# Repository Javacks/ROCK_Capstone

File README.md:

# ROCK_Capstone_Project
 This repository contains the electrical (only) designs made by me. 

 # The Objective
 The purpose of the project is to create an cave ROV (Remote Operated Vehicle) explorer capable of handling temperatures up to 50°C. This with the intent to avoid miners to traverse dangerous zones where heat or dangerous gases are present. The ROV is able to traverse up to 50m in distance, by controlling it safely at a central computer. The computer and the ROV are communicating through a CAT6 (Ethernet) cable.

 # Some Technical Details
The ROV is able to measure 4 different gases known to damage the human body: $CH_4, $CO_2, CO, H_2S$.
- All gases are measured in ppm (parts per million)
- All gases readings are in real time

Due to different power rails, and different demands, this project contains a custom __daughter board for the STM32: NUCLEO-64 STM32F446RE__. The document refers this custom PCB as the "STM32_Shield".

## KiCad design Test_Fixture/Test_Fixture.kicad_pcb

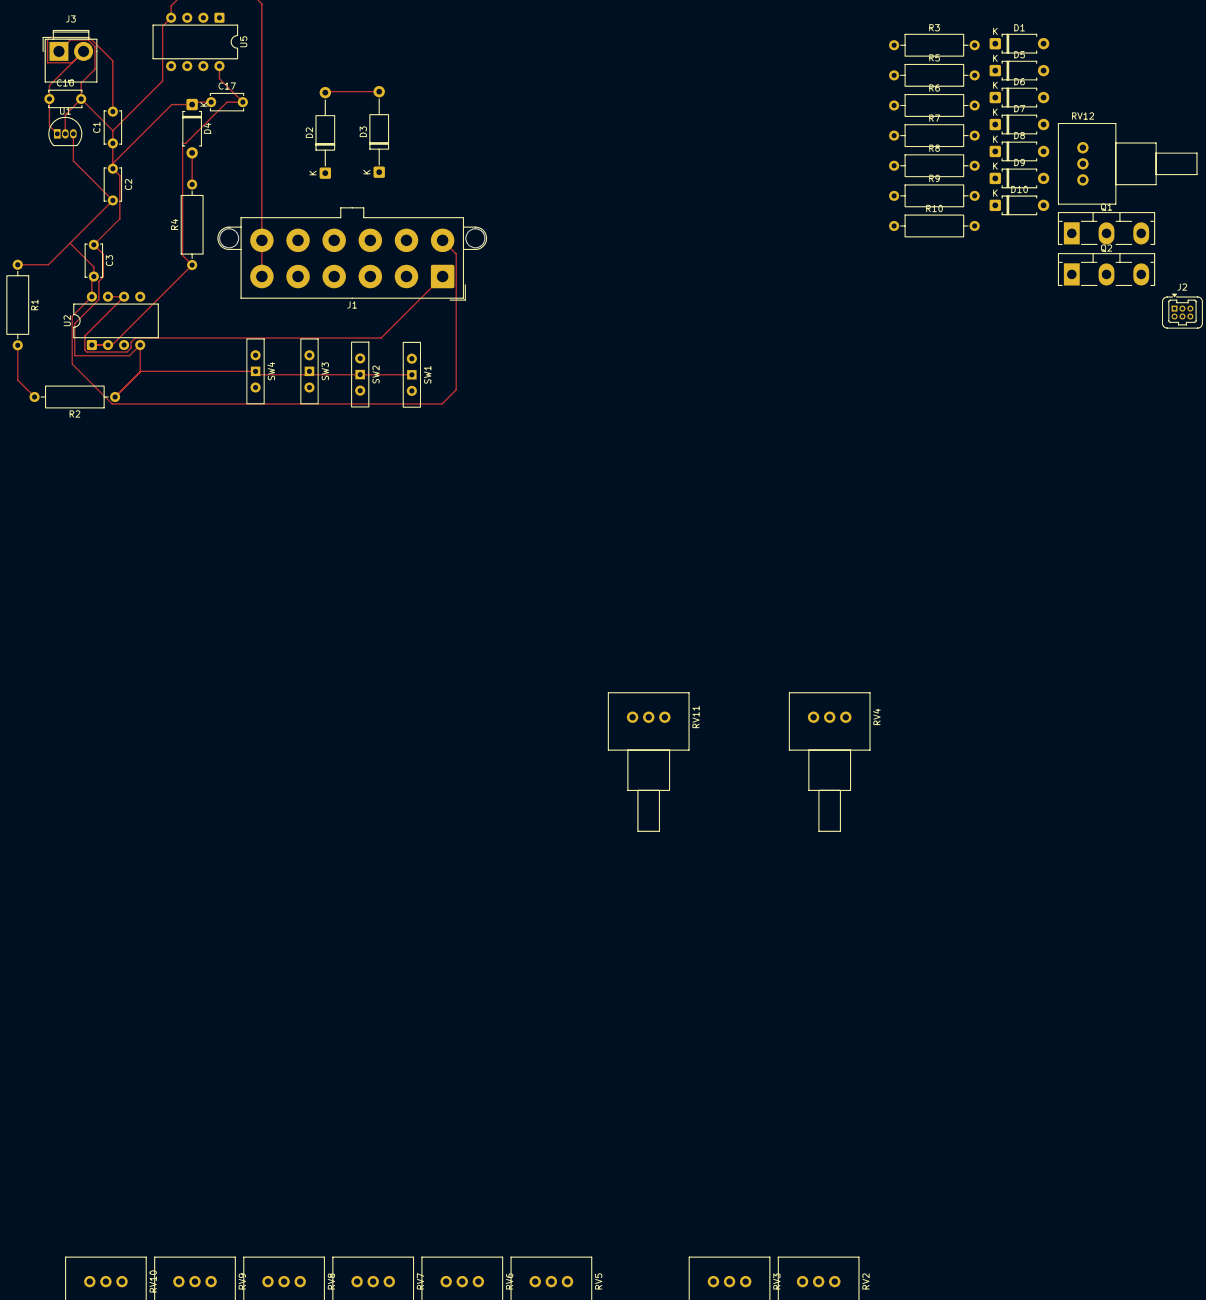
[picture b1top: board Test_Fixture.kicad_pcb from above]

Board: 2 copper layers, 48 parts (0 on the bottom side), 36 nets.

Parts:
C1, C2: 0.2; C_Disc_D5.0mm_W2.5mm_P5.00mm
C3, C17: 0.1; C_Disc_D5.0mm_W2.5mm_P5.00mm
C16: 100; C_Disc_D5.0mm_W2.5mm_P5.00mm
D1, D4, D5, D6, D7, D8, D9, D10: LED; D_A-405_P7.62mm_Horizontal
D2, D3: D; D_A-405_P12.70mm_Horizontal
J1: Analog Signals; Molex_Mega-Fit_76829-0012_2x06_P5.70mm_Vertical
J2: Digital Signals; Harwin_Gecko-G125-FVX0605L0X_2x03_P1.25mm_Vertical
J3: Power Supply; JWT_A3963_1x02_P3.96mm_Vertical
Q1, Q2: 2N222; TO-218-3_Vertical
R1: 2.2k; R_Axial_DIN0309_L9.0mm_D3.2mm_P12.70mm_Horizontal
R2: 4.7k; R_Axial_DIN0309_L9.0mm_D3.2mm_P12.70mm_Horizontal
R3, R4, R5, R6, R7, R8, R9, R10: 220; R_Axial_DIN0309_L9.0mm_D3.2mm_P12.70mm_Horizontal
RV2, RV3, RV4, RV5, RV6, RV7, RV8, RV9, RV10: 10k; Potentiometer_Vishay_148-149_Single_Horizontal
RV11, RV12: 5k; Potentiometer_Vishay_148-149_Single_Horizontal
SW1, SW2, SW3, SW4: SW_SPST; SW_Slide-03_Wuerth-WS-SLTV_10x2.5x6.4_P2.54mm
U1: LM78L05_SO8; TO-92_Inline
U2, U5: LM358; CERDIP-8_W7.62mm_SideBrazed

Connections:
+3.3V: C17.2, D1.2 (A), D5.2 (A), D6.2 (A), D7.2 (A), D8.2 (A), R4.1, R9.1, R10.1, RV4.1, U2.1, U2.2 (-), U5.8 (V+)
+5V: C2.2, C3.2, J1.2, R1.1, U1.3 (VO), U2.8 (V+)
+24V: C1.2, C16.1, J3.2, U1.1 (VI)
/3.3_Adjust: J1.1, U2.6 (-), U2.7
/Digital & LED signals/3.3_Adjust: RV11.1, RV12.1
/Digital & LED signals/Baro_Fault: J2.6, Q2.2 (B)
/Digital & LED signals/Hum_Fault: J2.1, Q1.2 (B)
/Digital & LED signals/MotorOk: J2.4, R7.2, SW3.2 (B)
/Digital & LED signals/PowerOK: J2.5, R8.2, SW4.2 (B)
/Digital & LED signals/~Temp_Fault1: D2.1 (K), J2.2, R5.2, SW1.2 (B), U5.7
/Digital & LED signals/~Temp_Fault2: D3.1 (K), J2.3, R6.2, SW2.2 (B), U5.1
/Volt_Loss_Distance: RV2.1, RV3.1, RV5.1, RV6.1, RV7.1, RV8.1, RV9.1, RV10.1
GND: C1.1, C2.1, C3.1, C16.2, C17.1, D4.1 (K), J1.11, J1.12, J3.1, Q1.3 (E), Q2.3 (E), R2.1, RV2.3, RV3.3, RV4.3, RV5.3, RV6.3, RV7.3, RV8.3, RV9.3, RV10.3, RV11.3, RV12.3, SW1.1 (A), SW2.1 (A), SW3.1 (A), SW4.1 (A), U1.2 (GND), U2.4 (V-), U5.4 (V-)
unnamed: D1.1 (K), R3.1
unnamed: D2.2 (A), D3.2 (A), R3.2
unnamed: D4.2 (A), R4.2
unnamed: D5.1 (K), R5.1
unnamed: D6.1 (K), R6.1
unnamed: D7.1 (K), R7.1
unnamed: D8.1 (K), R8.1
unnamed: D9.2 (A), R10.2
unnamed: D9.1 (K), Q1.1 (C)
unnamed: D10.2 (A), R9.2
unnamed: D10.1 (K), Q2.1 (C)
unnamed: J1.5, RV5.2
unnamed: J1.6, RV2.2
unnamed: J1.7, RV3.2
unnamed: J1.8, RV6.2
unnamed: J1.9, RV7.2
unnamed: J1.10, RV8.2
unnamed: R1.2, R2.2, U2.3 (+)
unnamed: RV4.2, U2.5 (+)
unnamed: RV12.2, U5.2 (-)
unnamed: RV11.2, U5.6 (-)
Temp1: J1.3, RV10.2, U5.3 (+), U5.5 (+)
Temp2: J1.4, RV9.2

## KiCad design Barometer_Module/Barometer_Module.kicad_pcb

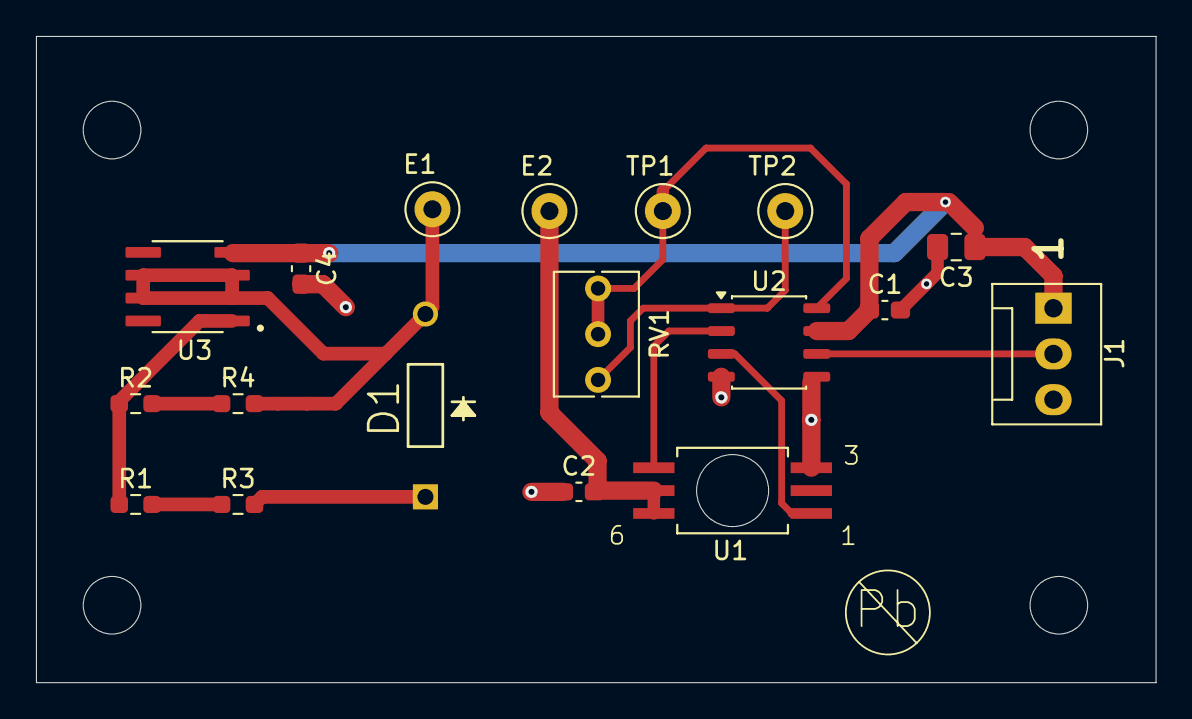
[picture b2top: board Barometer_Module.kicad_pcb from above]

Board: 2 copper layers, 62.2 x 35.9 mm, 22 parts (0 on the bottom side), 13 nets.

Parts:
C1, C2, C4: 0.1u; C_0603_1608Metric_Pad1.08x0.95mm_HandSolder
C3: 6.8u; C_0805_2012Metric_Pad1.18x1.45mm_HandSolder
D1: 1N457; DIO_1N457
E1, E2: TestPoint; TestPoint_Loop_D2.50mm_Drill1.0mm
H1, H2, H3, H4: MountingHole_Pad; MountingHole_3.2mm_M3_ISO7380
J1: 0022112032; FanPinHeader_1x03_P2.54mm_Vertical
R1: 1k; R_0603_1608Metric_Pad0.98x0.95mm_HandSolder
R2: 10k; R_0603_1608Metric_Pad0.98x0.95mm_HandSolder
R3: 330; R_0603_1608Metric_Pad0.98x0.95mm_HandSolder
R4: 3.3k; R_0603_1608Metric_Pad0.98x0.95mm_HandSolder
RV1: 10k; Potentiometer_Bourns_3266Y_Vertical
TP1, TP2: RV1; TestPoint_Loop_D2.50mm_Drill1.0mm
U1: 2SMPP-03; XDCR_2SMPP-03
U2: INA126UA; JEITA_SOIC-8_3.9x4.9mm_P1.27mm
U3: LM334MX_NOPB; SOIC127P599X175-8N

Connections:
+3.3V: C1.1, C3.1, C4.1, J1.1, U2.7 (V+), U3.4 (V+)
Earth: C1.2, C2.1, C3.2, C4.2, J1.3, U1.3 (GND), U2.4 (V-), U2.5 (Ref)
unnamed: D1.2 (A), R3.2
unnamed: D1.1 (K), E1.1, R4.2, U3.2 (V-_2), U3.3 (V-_3), U3.6 (V-_6), U3.7 (V-_7)
unnamed: J1.2, U2.6
unnamed: R1.2, R3.1
unnamed: R2.2, R4.1
unnamed: RV1.1, TP2.1, U2.1 (Rg)
unnamed: RV1.2, RV1.3, TP1.1, U2.8 (Rg)
unnamed: C2.2, E2.1, U1.5 (N-SUB), U1.6 (ICC)
unnamed: U1.1 (VOUT+), U2.3 (+)
unnamed: U1.4 (VOUT-), U2.2 (-)
unnamed: R1.1, R2.1, U3.1 (R)

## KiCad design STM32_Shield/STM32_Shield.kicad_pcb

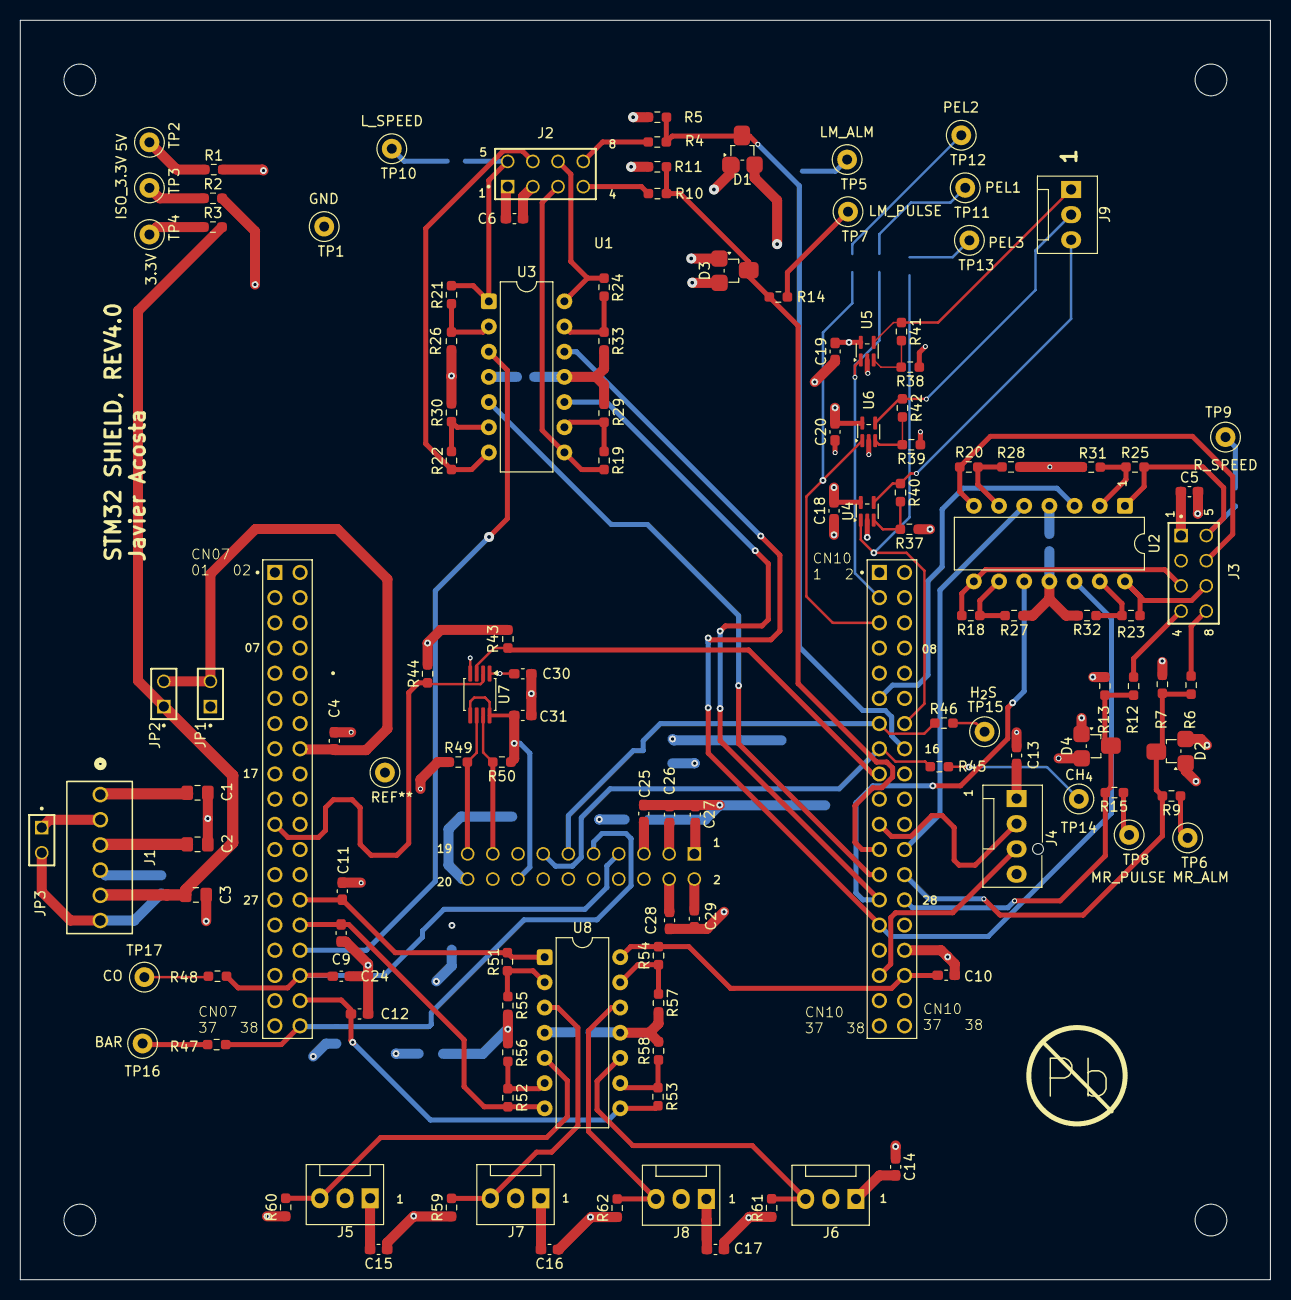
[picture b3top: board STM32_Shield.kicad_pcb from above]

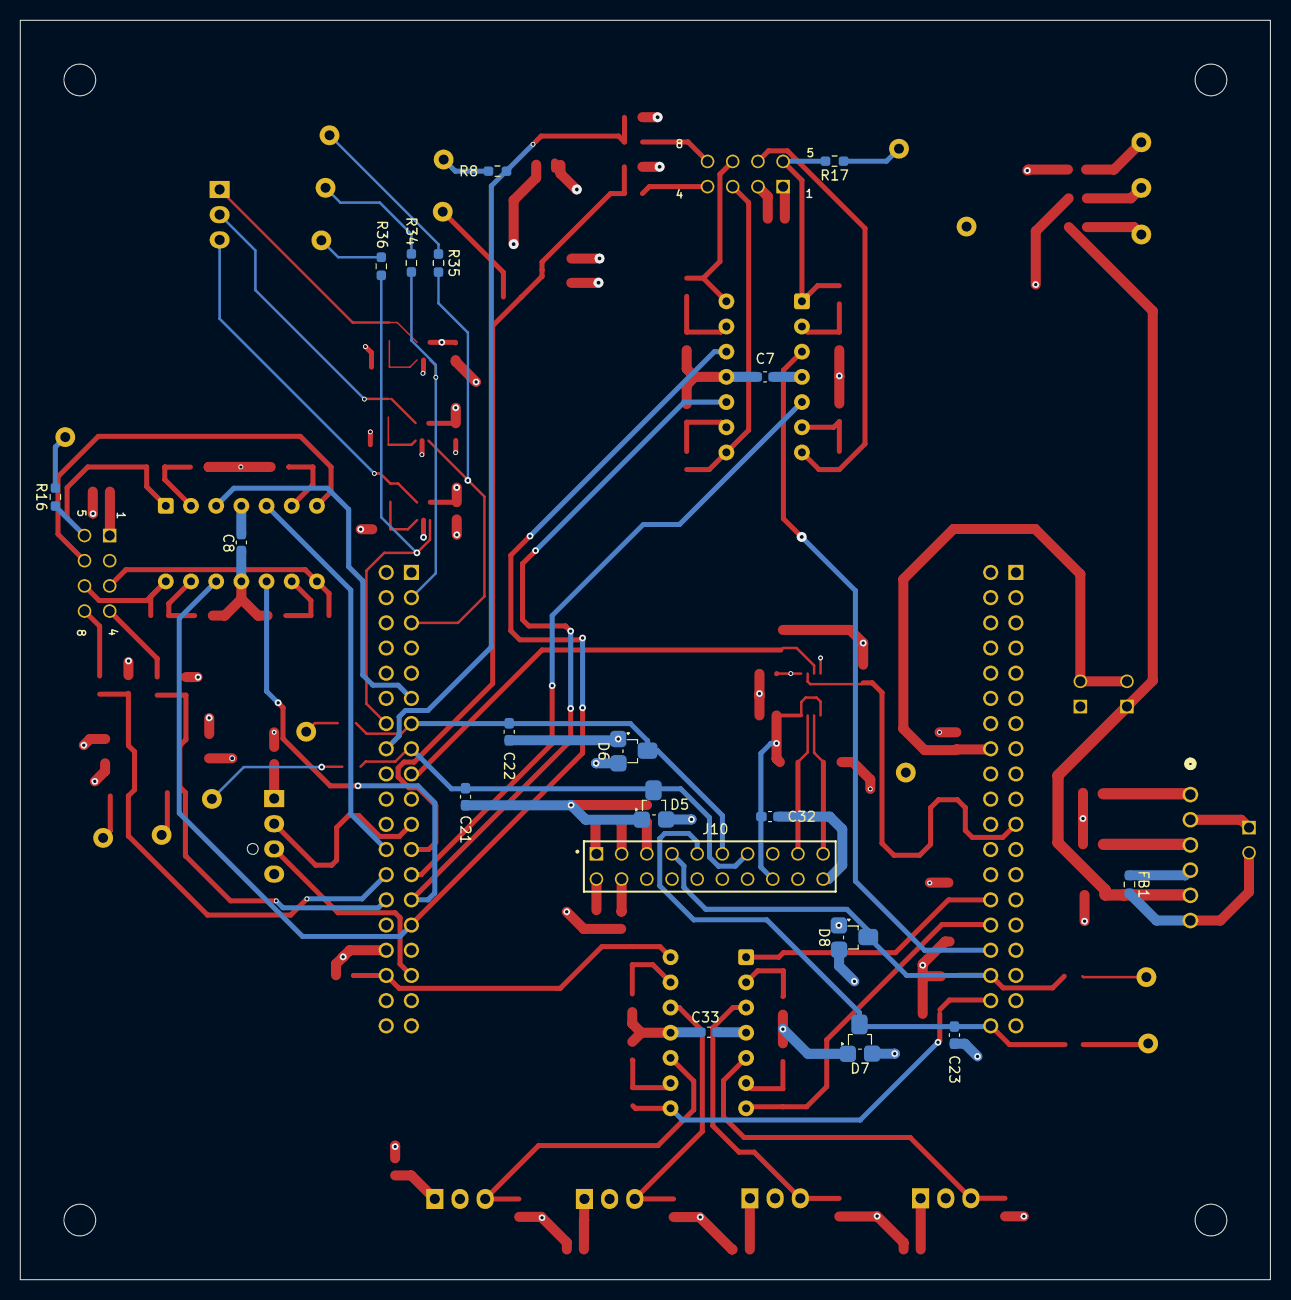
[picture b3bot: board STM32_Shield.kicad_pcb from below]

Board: 4 copper layers, 126.1 x 127.0 mm, 146 parts (19 on the bottom side), 83 nets.

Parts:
C1, C2, C3: 6.8u; C_0805_2012Metric_Pad1.18x1.45mm_HandSolder
C4, C5, C6, C7, C8, C9, C10, C11, C12, C13, C14, C15, C16, C17, C18, C19, C20, C21, C22, C23, C24, C25, C26, C27, C28, C29, C30, C31, C32, C33: 0.1u; C_0603_1608Metric_Pad1.08x0.95mm_HandSolder
D1, D2, D3, D4, D5, D6, D7, D8: BAT30SWFILM; SOT-323_SC-70_Hand_Soldering
FB1: NFZ2MSD101SZ10L; R_0603_1608Metric_Pad0.98x0.95mm_HandSolder
H1, H2, H3, H4: MountingHole_Pad; MountingHole_3.2mm_M3_ISO14580
J1: 0022112062; CONN_A-6373-06A_MOL
J2, J3: TSW-104-07-F-D; SAMTEC_TSW-104-07-F-D
J4: 0022112042; FanPinHeader_1x04_P2.54mm_Vertical
J5, J6, J7, J8, J9: 0022112032; FanPinHeader_1x03_P2.54mm_Vertical
J10: TSW-110-07-F-D; SAMTEC_TSW-110-07-F-D
JP1, JP2, JP3: TSW-102-07-F-S; SAMTEC_TSW-102-07-F-S
R1, R2, R3, R8, R9, R14, R15, R16, R17, R18, R19, R20, R21, R22, R23, R24, R25, R26, R27, R28, R29, R30, R31, R32, R33, R34, R35, R36, R37, R38, R39, R40, R41, R42, R45, R46, R47, R48, R51, R52, R53, R54, R55, R56, R57, R58: 10k; R_0603_1608Metric_Pad0.98x0.95mm_HandSolder
R4, R6, R10, R12, R43, R44, R49, R50: 2.2k; R_0603_1608Metric_Pad0.98x0.95mm_HandSolder
R5, R7, R11, R13: 4.7k; R_0603_1608Metric_Pad0.98x0.95mm_HandSolder
R59, R60, R61, R62: 1k; R_0603_1608Metric_Pad0.98x0.95mm_HandSolder
TP1: GND; TestPoint_Loop_D2.50mm_Drill1.0mm
TP2: 5V; TestPoint_Loop_D2.50mm_Drill1.0mm
TP3: ISO_3.3V; TestPoint_Loop_D2.50mm_Drill1.0mm
TP4: 3.3V; TestPoint_Loop_D2.50mm_Drill1.0mm
TP5: LM_ALM; TestPoint_Loop_D2.50mm_Drill1.0mm
TP6: MR_ALM; TestPoint_Loop_D2.50mm_Drill1.0mm
TP7: LM_PULSE; TestPoint_Loop_D2.50mm_Drill1.0mm
TP8: MR_PULSE; TestPoint_Loop_D2.50mm_Drill1.0mm
TP9: R_SPEED; TestPoint_Loop_D2.50mm_Drill1.0mm
TP10: L_SPEED; TestPoint_Loop_D2.50mm_Drill1.0mm
TP11: PEL1; TestPoint_Loop_D2.50mm_Drill1.0mm
TP12: PEL2; TestPoint_Loop_D2.50mm_Drill1.0mm
TP13: PEL3; TestPoint_Loop_D2.50mm_Drill1.0mm
TP14: CH_{4}; TestPoint_Loop_D2.50mm_Drill1.0mm
TP15: H_{2}S; TestPoint_Loop_D2.50mm_Drill1.0mm
TP16: BAR; TestPoint_Loop_D2.50mm_Drill1.0mm
TP17: CO; TestPoint_Loop_D2.50mm_Drill1.0mm
U1: NUCLEO-F446RE; MODULE_NUCLEO-F446RE
U2, U3, U8: TL084HIDYYR; CERDIP-14_W7.62mm_SideBrazed
U4, U5, U6: TLV172IDCK; SOT-353_SC-70-5
U7: TPT29617A-VS1R; MSOP-8_3x3mm_P0.65mm

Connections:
+3.3V: C3.1, C14.2, C15.2, C16.2, C17.2, C25.2, C26.2, C27.2, C28.2, C29.2, C33.1, D5.2 (K), D6.2 (K), D7.2 (K), D8.2 (K), J1.5, J5.1, J6.1, J7.1, J8.1, J10.01, J10.02, J10.03, J10.04, J10.05, JP2.01, R3.2, U8.4 (V+)
+5V: C1.1, C5.1, C6.1, C7.1, C8.2, C13.1, C18.2, C19.2, C20.2, C31.1, C32.2, J1.1, J2.01, J3.01, J4.1, J10.16, R1.2, R49.1, R50.1, U2.4 (V+), U3.4 (V+), U4.5 (V+), U5.5 (V+), U6.5 (V+), U7.5 (DIR), U7.8 (VCCB)
CN07-21: R44.2, U1.CN7_21 (PB7), U7.2 (1A)
CN07-28: C11.2, R51.2, U1.CN7_28 (PA0), U8.1
CN07-30: C9.2, R52.2, U1.CN7_30 (PA1), U8.7
CN07-32: U1.CN7_32 (PA4), U3.3 (+)
CN07-34: C24.1, D8.3 (common), J10.07, R48.2, U1.CN7_34 (PB0)
CN07-36: C12.1, R53.2, U1.CN7_36 (PC1/PB9), U8.8
CN07-38: C23.1, D7.3 (common), J10.09, R47.2, U1.CN7_38 (PC0/PB8)
CN10-03: R34.1, U1.CN10_3 (PB8), U5.1 (+)
CN10-05: R35.1, U1.CN10_5 (PB9), U6.1 (+)
CN10-11: U1.CN10_11 (PA5), U2.3 (+)
CN10-13: C22.1, D6.3 (common), J10.11, R46.2, U1.CN10_13 (PA6)
CN10-14: R36.1, U1.CN10_14 (PA11), U4.1 (+)
CN10-15: C21.1, D5.3 (common), J10.13, R45.2, U1.CN10_15 (PA7)
CN10-16: D1.3 (common), R4.2, R5.1, R8.2, U1.CN10_16 (PB12)
CN10-17: R43.2, U1.CN10_17 (PB6), U7.3 (2A)
CN10-21: J4.2, U1.CN10_21 (PA9)
CN10-23: D3.3 (common), R10.2, R11.1, R14.2, U1.CN10_23 (PA8)
CN10-24: U1.CN10_24 (PB1), U2.5 (+)
CN10-25: U1.CN10_25 (PB10), U3.5 (+)
CN10-26: D2.3 (common), R6.1, R7.1, R9.2, U1.CN10_26 (PB15)
CN10-27: U1.CN10_27 (PB4), U2.10 (+), U3.10 (+)
CN10-28: D4.3 (common), R12.1, R13.1, R15.2, U1.CN10_28 (PB14)
CN10-29: U1.CN10_29 (PB5), U2.12 (+), U3.12 (+)
CN10-33: J4.3, U1.CN10_33 (PA10)
CN10-34: C10.1, R54.2, U1.CN10_34 (PC4), U8.14
Earth: C3.2, C9.1, C10.2, C11.1, C12.2, C14.1, C15.1, C16.1, C17.1, C21.2, C22.2, C23.2, C24.2, C25.1, C26.1, C27.1, C28.1, C29.1, C33.2, D5.1 (A), D6.1 (A), D7.1 (A), D8.1 (A), FB1.2, J1.6, J10.10, J10.12, J10.14, JP3.02, R55.2, R56.2, R57.2, R58.2, R59.1, R60.1, R61.1, R62.1, U1.CN10_32 (AGND), U8.11 (V-)
GND: C1.2, C2.2, C4.2, C5.2, C6.2, C7.2, C8.1, C13.2, C18.1, C19.1, C20.1, C30.2, C31.2, C32.1, D1.1 (A), D2.1 (A), D3.1 (A), D4.1 (A), FB1.1, J1.2, J1.4, J2.02, J3.02, J4.4, J10.20, JP3.01, R5.2, R7.2, R11.2, R13.2, R26.2, R27.2, R28.2, R29.2, R30.2, R31.2, R32.2, R33.2, R37.1, R38.1, R39.1, TP1.1, U1.CN7_8 (CN7_GND), U1.CN7_19 (CN7_GND), U1.CN7_20 (CN7_GND), U1.CN7_22 (CN7_GND), U1.CN10_9 (CN10_GND), U1.CN10_20 (CN10_GND), U2.11 (V-), U3.11 (V-), U4.2 (V-), U5.2 (V-), U6.2 (V-), U7.4 (GND)
ISO_+3.3V: C2.1, C30.1, D1.2 (K), D2.2 (K), D3.2 (K), D4.2 (K), J1.3, JP1.01, R2.2, R43.1, R44.1, U7.1 (VCCA)
unnamed: J2.03, R19.2, U3.8
unnamed: J2.04, R10.1
unnamed: J2.05, R17.2, R21.2, U3.1
unnamed: J2.06, R22.2, U3.7
unnamed: J2.07, R24.2, U3.14
unnamed: J2.08, R4.1
unnamed: J3.03, R18.2, U2.8
unnamed: J3.04, R12.2
unnamed: J3.05, R16.2, R25.2, U2.1
unnamed: J3.06, R20.2, U2.7
unnamed: J3.07, R23.2, U2.14
unnamed: J3.08, R6.2
unnamed: J5.3, R60.2, U8.5 (+)
unnamed: J6.3, R61.2, U8.10 (+)
unnamed: J7.3, R59.2, U8.3 (+)
unnamed: J8.3, R62.2, U8.12 (+)
unnamed: J9.1, R41.1, U5.4
unnamed: J9.2, R42.1, U6.4
unnamed: J9.3, R40.1, U4.4
unnamed: J10.17, R50.2, U7.7 (1B)
unnamed: J10.19, R49.2, U7.6 (2B)
unnamed: C4.1, JP1.02, JP2.02, U1.CN7_16 (CN7_+3V3)
unnamed: R1.1, TP2.1
unnamed: R2.1, TP3.1
unnamed: R3.1, TP4.1
unnamed: R8.1, TP5.1
unnamed: R9.1, TP6.1
unnamed: R14.1, TP7.1
unnamed: R15.1, TP8.1
unnamed: R16.1, TP9.1
unnamed: R17.1, TP10.1
unnamed: R34.2, TP11.1
unnamed: R35.2, TP12.1
unnamed: R36.2, TP13.1
unnamed: R45.1, TP14.1
unnamed: R46.1, TP15.1
unnamed: R47.1, TP16.1
unnamed: R48.1, TP17.1
unnamed: R25.1, R31.1, U2.2 (-)
unnamed: R20.1, R28.1, U2.6 (-)
unnamed: R18.1, R27.1, U2.9 (-)
unnamed: R23.1, R32.1, U2.13 (-)
unnamed: R21.1, R26.1, U3.2 (-)
unnamed: R22.1, R30.1, U3.6 (-)
unnamed: R19.1, R29.1, U3.9 (-)
unnamed: R24.1, R33.1, U3.13 (-)
unnamed: R37.2, R40.2, U4.3 (-)
unnamed: R38.2, R41.2, U5.3 (-)
unnamed: R39.2, R42.2, U6.3 (-)
unnamed: R51.1, R55.1, U8.2 (-)
unnamed: R52.1, R56.1, U8.6 (-)
unnamed: R53.1, R58.1, U8.9 (-)
unnamed: R54.1, R57.1, U8.13 (-)

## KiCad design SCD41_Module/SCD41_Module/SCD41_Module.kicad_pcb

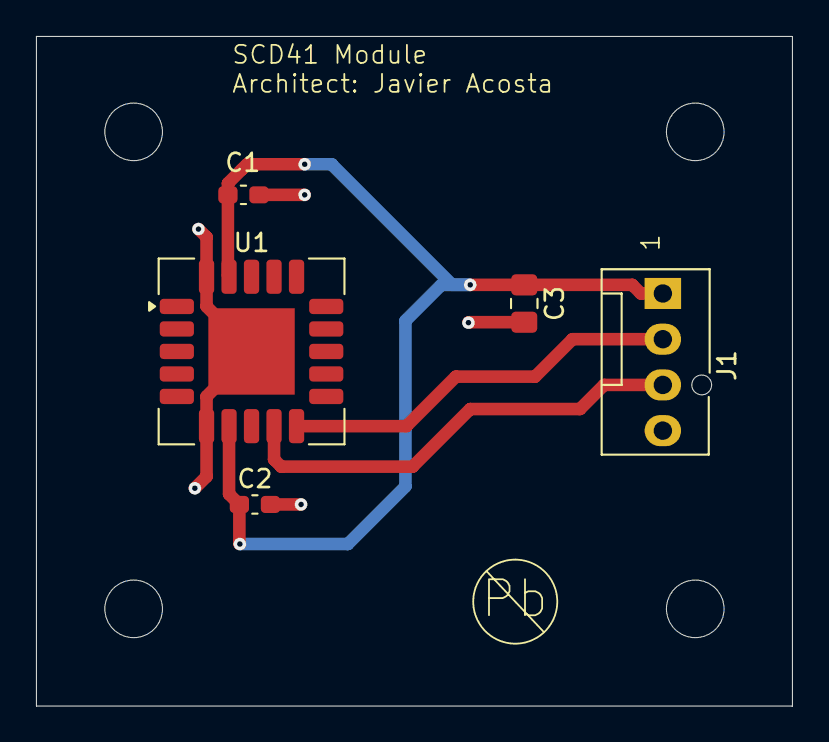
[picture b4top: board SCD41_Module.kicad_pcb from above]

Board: 2 copper layers, 42.0 x 37.2 mm, 9 parts (0 on the bottom side), 4 nets.

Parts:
C1, C2: 0.1u; C_0603_1608Metric_Pad1.08x0.95mm_HandSolder
C3: 6.8u; C_0805_2012Metric_Pad1.18x1.45mm_HandSolder
H1, H2, H3, H4: MountingHole_Pad; MountingHole_3.2mm_M3_ISO14580
J1: 0022112042; FanPinHeader_1x04_P2.54mm_Vertical
U1: SCD41-D-R2; Sensirion_SCD4x-1EP_10.1x10.1mm_P1.25mm_EP4.8x4.8mm

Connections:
+5V: C1.1, C2.1, C3.1, J1.1, U1.7 (VDD), U1.19 (VDD)
GND: C1.2, C2.2, C3.2, J1.4, U1.6 (GND), U1.20 (GND), U1.21 (GND)
unnamed: J1.2, U1.10 (SDA)
unnamed: J1.3, U1.9 (SCL)

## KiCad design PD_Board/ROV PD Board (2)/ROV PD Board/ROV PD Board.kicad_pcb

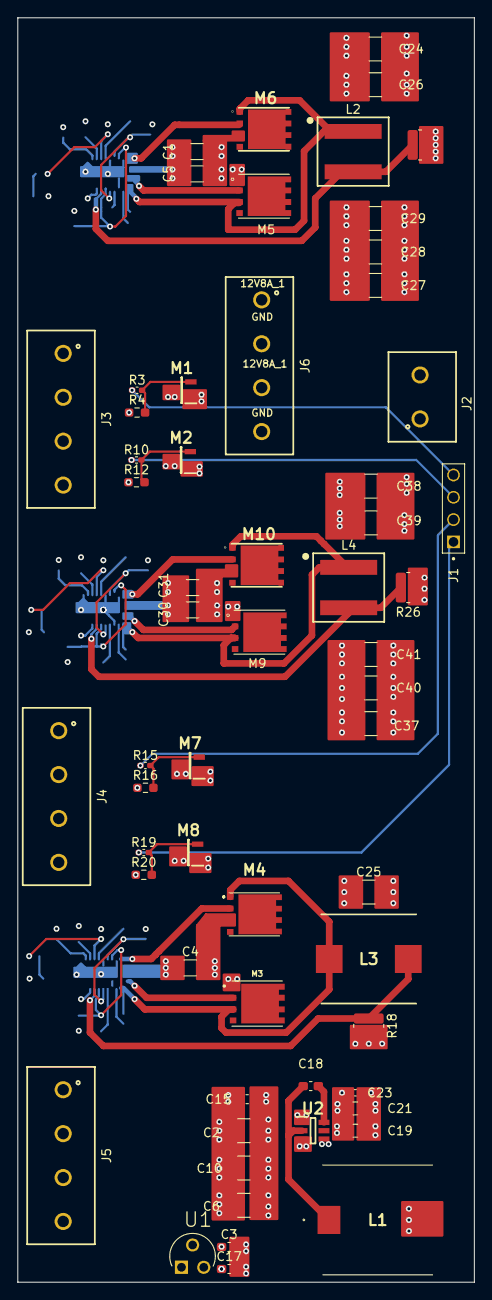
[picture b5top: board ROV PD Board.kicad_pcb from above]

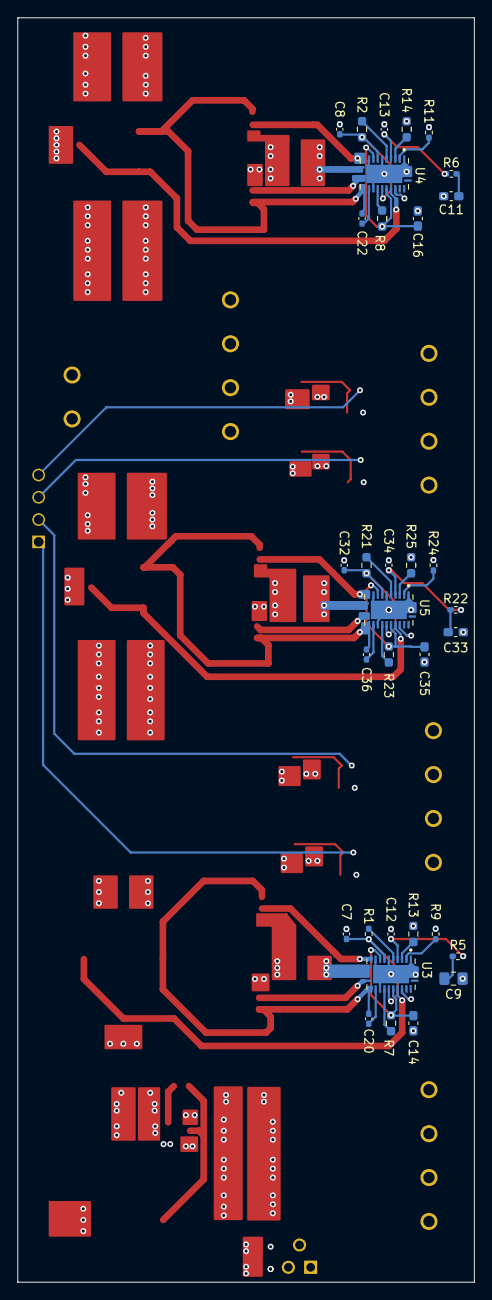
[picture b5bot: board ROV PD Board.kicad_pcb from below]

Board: 4 copper layers, 52.0 x 144.0 mm, 92 parts (33 on the bottom side), 60 nets.

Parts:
C1, C4, C5, C30, C31: 4.7 uF; C_1206_3216Metric_Pad1.33x1.80mm_HandSolder
C2, C6, C10: 10.0 uF; C_1210_3225Metric_Pad1.33x2.70mm_HandSolder
C3: 1.0 uF; C_0603_1608Metric_Pad1.08x0.95mm_HandSolder
C7, C8, C22, C23, C32, C36: 100.0 nF; C_0402_1005Metric_Pad0.74x0.62mm_HandSolder
C9: 3.9 nF; C_0805_2012Metric_Pad1.18x1.45mm_HandSolder
C11, C33: 3.0 nF; C_0603_1608Metric_Pad1.08x0.95mm_HandSolder
C12: 110.0 pF; C_0402_1005Metric_Pad0.74x0.62mm_HandSolder
C13, C34: 150.0 pF; C_0402_1005Metric_Pad0.74x0.62mm_HandSolder
C14, C16, C17, C35: 2.2 uF; C_0603_1608Metric_Pad1.08x0.95mm_HandSolder
C15, C18: 100 nF; C_0603_1608Metric_Pad1.08x0.95mm_HandSolder
C19, C21: 22.0 nF; C_0805_2012Metric_Pad1.18x1.45mm_HandSolder
C20: 100 nF; C_0402_1005Metric_Pad0.74x0.62mm_HandSolder
C24, C26, C27, C28, C29, C37, C38, C39, C40, C41: 22.0 uF; C_1210_3225Metric_Pad1.33x2.70mm_HandSolder
C25: 47.0 uF; C_1210_3225Metric_Pad1.33x2.70mm_HandSolder
J1: Conn_01x04; WURTH_61300411121
J2: 691137710002
J3, J4, J6: 691137710004
J5: 691137710006; 691137710004
L1: 15.0 uH; SLF12575
L2, L4: 4.7 uH; WE-XHMI_7070
L3: 4.7 uH; INDPM108102X400N
M1, M2, M7, M8: NMOS; SOT95P237X112-3N
M3: NMOS; TRANS_CSD18534Q5A
M4: NMOS; CSD18514Q5A
M5, M9: NMOS; MOSFET_CSD19531Q5A
M6, M10: NMOS; Q5A_VSON-FET
R1: 24.9 kOhm; R_0402_1005Metric_Pad0.72x0.64mm_HandSolder
R2, R21: 47.5 kOhm; R_0603_1608Metric_Pad0.98x0.95mm_HandSolder
R3, R10, R15, R19: 470 Ohm; C_0402_1005Metric_Pad0.74x0.62mm_HandSolder
R4, R12, R16, R20: 47 kOhm; R_0603_1608Metric_Pad0.98x0.95mm_HandSolder
R5: 4.87 kOhm; R_0402_1005Metric_Pad0.72x0.64mm_HandSolder
R6, R22: 8.66 kOhm; R_0402_1005Metric_Pad0.72x0.64mm_HandSolder
R7, R8, R23: 100.0 kOhm; R_0603_1608Metric_Pad0.98x0.95mm_HandSolder
R9, R11, R24: 41.2 kOhm; R_0402_1005Metric_Pad0.72x0.64mm_HandSolder
R13, R14, R25: 42.2 kOhm; R_0603_1608Metric_Pad0.98x0.95mm_HandSolder
R17, R26: 6.0 mOhm; R_0612_1632Metric_Pad1.18x3.40mm_HandSolder
R18: 9.0 mOhm; R_0612_1632Metric_Pad1.18x3.40mm_HandSolder
U1: MCP1700-3302E_TO; TO127P254X495-3
U2: TPS54202DDCR; SOT95P280X110-6N
U3, U4, U5: LM5148RGYR; QFN50P550X350X100-25N

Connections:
+3.3V250mA: C17.1, J5.3, U1.3 (VOUT)
+5V1A: C3.1, C19.1, C21.1, C23.1, J5.2, L1.2, U1.2 (VIN), U2.4 (FB)
+5V5A: C25.1, J5.1, R18.2, U3.21 (VOUT)
+12V8A_1: C24.1, C26.1, C27.1, C28.1, C29.1, J3.1, J3.3, J6.1, J6.3, R17.1, U4.21 (VOUT)
+12V8A_2: C37.1, C38.1, C39.1, C40.1, C41.1, J4.1, J4.3, R26.1, U5.21 (VOUT)
+24V: C1.1, C2.1, C4.1, C5.1, C6.1, C10.1, C15.1, C30.1, C31.1, J2.2, M3.1 (D), M5.1 (D), M9.1 (D), U2.3 (VIN), U3.12 (VIN), U4.12 (VIN), U5.12 (VIN)
/GPIO_A: J1.4, R3.1
GNDREF: C1.2, C2.2, C3.2, C4.2, C5.2, C6.2, C7.2, C8.2, C9.1, C10.2, C11.1, C12.1, C13.1, C14.2, C15.2, C16.2, C17.2, C19.2, C21.2, C23.2, C24.2, C25.2, C26.2, C27.2, C28.2, C29.2, C30.2, C31.2, C32.2, C33.1, C34.1, C35.2, C37.2, C38.2, C39.2, C40.2, C41.2, J2.1, J5.4, J6.2, J6.4, M1.3 (S), M2.3 (S), M4.3 (S), M6.3 (S), M7.3 (S), M8.3 (S), M10.3 (S), R4.1, R9.2, R11.1, R12.1, R13.2, R14.1, R16.1, R20.1, R24.1, R25.1, U1.1 (GND), U2.1 (GND), U3.1 (NC), U3.2 (NC__1), U3.7 (AGND), U3.10 (PGND), U3.16 (VCCX), U3.25 (EP), U4.1 (NC), U4.2 (NC__1), U4.7 (AGND), U4.10 (PGND), U4.16 (VCCX), U4.25 (EP), U5.1 (NC), U5.2 (NC__1), U5.7 (AGND), U5.10 (PGND), U5.16 (VCCX), U5.25 (EP)
GPIO_B: J1.3, R10.1
GPIO_C: J1.2, R15.1
GPIO_D: J1.1, R19.1
unnamed: C9.2, R5.1
unnamed: C11.2, R6.1
unnamed: C33.2, R22.1
unnamed: J3.2, M1.1 (D)
unnamed: M1.2 (G), R3.2, R4.2
unnamed: J3.4, M2.1 (D)
unnamed: M2.2 (G), R10.2, R12.2
unnamed: M3.2 (G), U3.13 (HO)
unnamed: C20.2, L3.1, M3.3 (S), M4.1 (D), U3.14 (SW)
unnamed: M4.2 (G), U3.11 (LO)
unnamed: M5.2 (G), U4.13 (HO)
unnamed: C22.1, L2.1, M5.3 (S), M6.1 (D), U4.14 (SW)
unnamed: M6.2 (G), U4.11 (LO)
unnamed: J4.2, M7.1 (D)
unnamed: M7.2 (G), R15.2, R16.2
unnamed: J4.4, M8.1 (D)
unnamed: M8.2 (G), R19.2, R20.2
unnamed: M9.2 (G), U5.13 (HO)
unnamed: C36.1, L4.1, M9.3 (S), M10.1 (D), U5.14 (SW)
unnamed: M10.2 (G), U5.11 (LO)
unnamed: C18.1, U2.6 (BOOT)
unnamed: C18.2, L1.1, U2.2 (SW)
unnamed: C20.1, U3.15 (CBOOT)
unnamed: R9.1, U3.3 (CNFG)
unnamed: C14.1, R7.1, U3.9 (VCC), U3.19 (EN)
unnamed: C12.2, R5.2, U3.5 (EXTCOMP)
unnamed: R1.1, U3.6 (FB)
unnamed: L3.2, R18.1, U3.20 (ISNS+)
unnamed: C7.1, R1.2, U3.8 (VDDA), U3.18 (PFM/SYNC)
unnamed: R7.2, U3.17 (PG/SYNCOUT)
unnamed: R13.1, U3.4 (RT)
unnamed: C22.2, U4.15 (CBOOT)
unnamed: R11.2, U4.3 (CNFG)
unnamed: C16.1, R8.1, U4.9 (VCC), U4.19 (EN)
unnamed: C13.2, R6.2, U4.5 (EXTCOMP)
unnamed: R2.1, U4.6 (FB)
unnamed: L2.2, R17.2, U4.20 (ISNS+)
unnamed: C8.1, R2.2, U4.8 (VDDA), U4.18 (PFM/SYNC)
unnamed: R8.2, U4.17 (PG/SYNCOUT)
unnamed: R14.2, U4.4 (RT)
unnamed: C36.2, U5.15 (CBOOT)
unnamed: R24.2, U5.3 (CNFG)
unnamed: C35.1, R23.1, U5.9 (VCC), U5.19 (EN)
unnamed: C34.2, R22.2, U5.5 (EXTCOMP)
unnamed: R21.1, U5.6 (FB)
unnamed: L4.2, R26.2, U5.20 (ISNS+)
unnamed: C32.1, R21.2, U5.8 (VDDA), U5.18 (PFM/SYNC)
unnamed: R23.2, U5.17 (PG/SYNCOUT)
unnamed: R25.2, U5.4 (RT)
